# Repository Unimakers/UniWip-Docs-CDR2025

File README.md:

---
title: "README & MICRODOC"
layout: default
---
# Documentation de l'équipe UniWIP

Table de contenu:
- [Documentation de l'équipe UniWIP](#documentation-de-léquipe-uniwip)
  - [Comment créer une page ?](#comment-créer-une-page-)
  - [Comment afficher un modèle 3D](#comment-afficher-un-modèle-3d)

## Comment créer une page ?

Allez dans le dossier correspondant au thème de la page, 

exemple pour l'élec du robot principal: Robot/Elec/

Créez un nouveau fichier pour votre nouvelle page.

Rajoutez en haut du fichier:

```yaml
---
title: "Titre de votre page"
layout: technical
---
```

Utilisez `layout: technical` si vous souhaitez utiliser les modèles 3D ou le visualiseur kicad dans votre page, sinon utilisez `layout: default` pour réduire le temps de chargement de la page en supprimant les imports inutiles.

Les clés de définition doivent se trouver entre les deux `---`.
Après le deuxième `---` vous pouvez écrire le contenu de la page **en markdown**.

Vous pouvez rajouter un 
```yaml
has_children: true
```
si vous souhaitez faire de cette page une page de catégorie qui aura donc des sous-pages.

Pour mettre cette page en tant que sous-page dans une catégorie (et non à la racine) vous devez rajouter une clé `parent` et eventuellement une clé `grand_parent`:

La clé `parent` permettra de définir le parent direct de la page, la valeur doit etre le titre de la page parent.

Exemple, si vous créez une page dans la catégorie `Electronique` du `Robot` vous devrez définir la clé `parent` avec la valeur `Electronique`.

La clé `grand_parent` permettra de définir le grand parent de la page, c'est à dire la catégorie racine, la valeur doit etre le titre du grand parent.

Exemple, si vous créez une page dans la catégorie `Electronique` du `Robot` vous devrez définir la clé `grand_parent` avec la valeur `Robot`

Actuellement l'arbre des titres et catégories est:
```
Racine:
|-Présentation
|-Robot:
| |-Mécanique
| |-Stratégie
|-Pami:
| |-Mécanique
| |-Stratégie
|-Electronique
|-Programmation
| |-Déplacement
| |-Détection
```

Exemple pour créer une catégorie `Actionneurs` dans `Mécanique` sous `Robot` et ensuite créer une page `Pince`:

On crée le dossier `Robot/Meca/Actionneurs` (c'est mieux pour la lisibilité de trier les pages dans des dossiers, techniquement on pourrait tout laisser à la racine).

On crée le fichier `Robot/Meca/Actionneurs/Actionneurs.md`:
```md
---
title: Actionneurs
parent: Mécanique
grand_parent: Robot
has_children: true
layout: default
---
# Les actionneurs de notre robot
Le robot a besoin d'actionneurs pour fonctionner
```

On crée le fichier `Robot/Meca/Actionneurs/Pince.md`:
```md
---
title: Pince
parent: Actionneurs
grand_parent: Mécanique
has_children: true
layout: default
---
# La pince du robot
La pince du robot, nécessaire pour attraper.....
```

## Comment afficher un modèle 3D

Dans votre code markdown rajoutez:
```md
<model-viewer alt="Texte de déscription du modèle 3D" src="url / chemin du modèle 3D" ar shadow-intensity="1" camera-controls touch-action="pan-y"></model-viewer>

Ou

{%raw%}{{%include model3D.html alt="Texte de description du modèle 3D" model="url / chemin du modèle 3D"%}}{%endraw%}
``` 
Le modèle 3D **doit** être en format GLTF / GLB.

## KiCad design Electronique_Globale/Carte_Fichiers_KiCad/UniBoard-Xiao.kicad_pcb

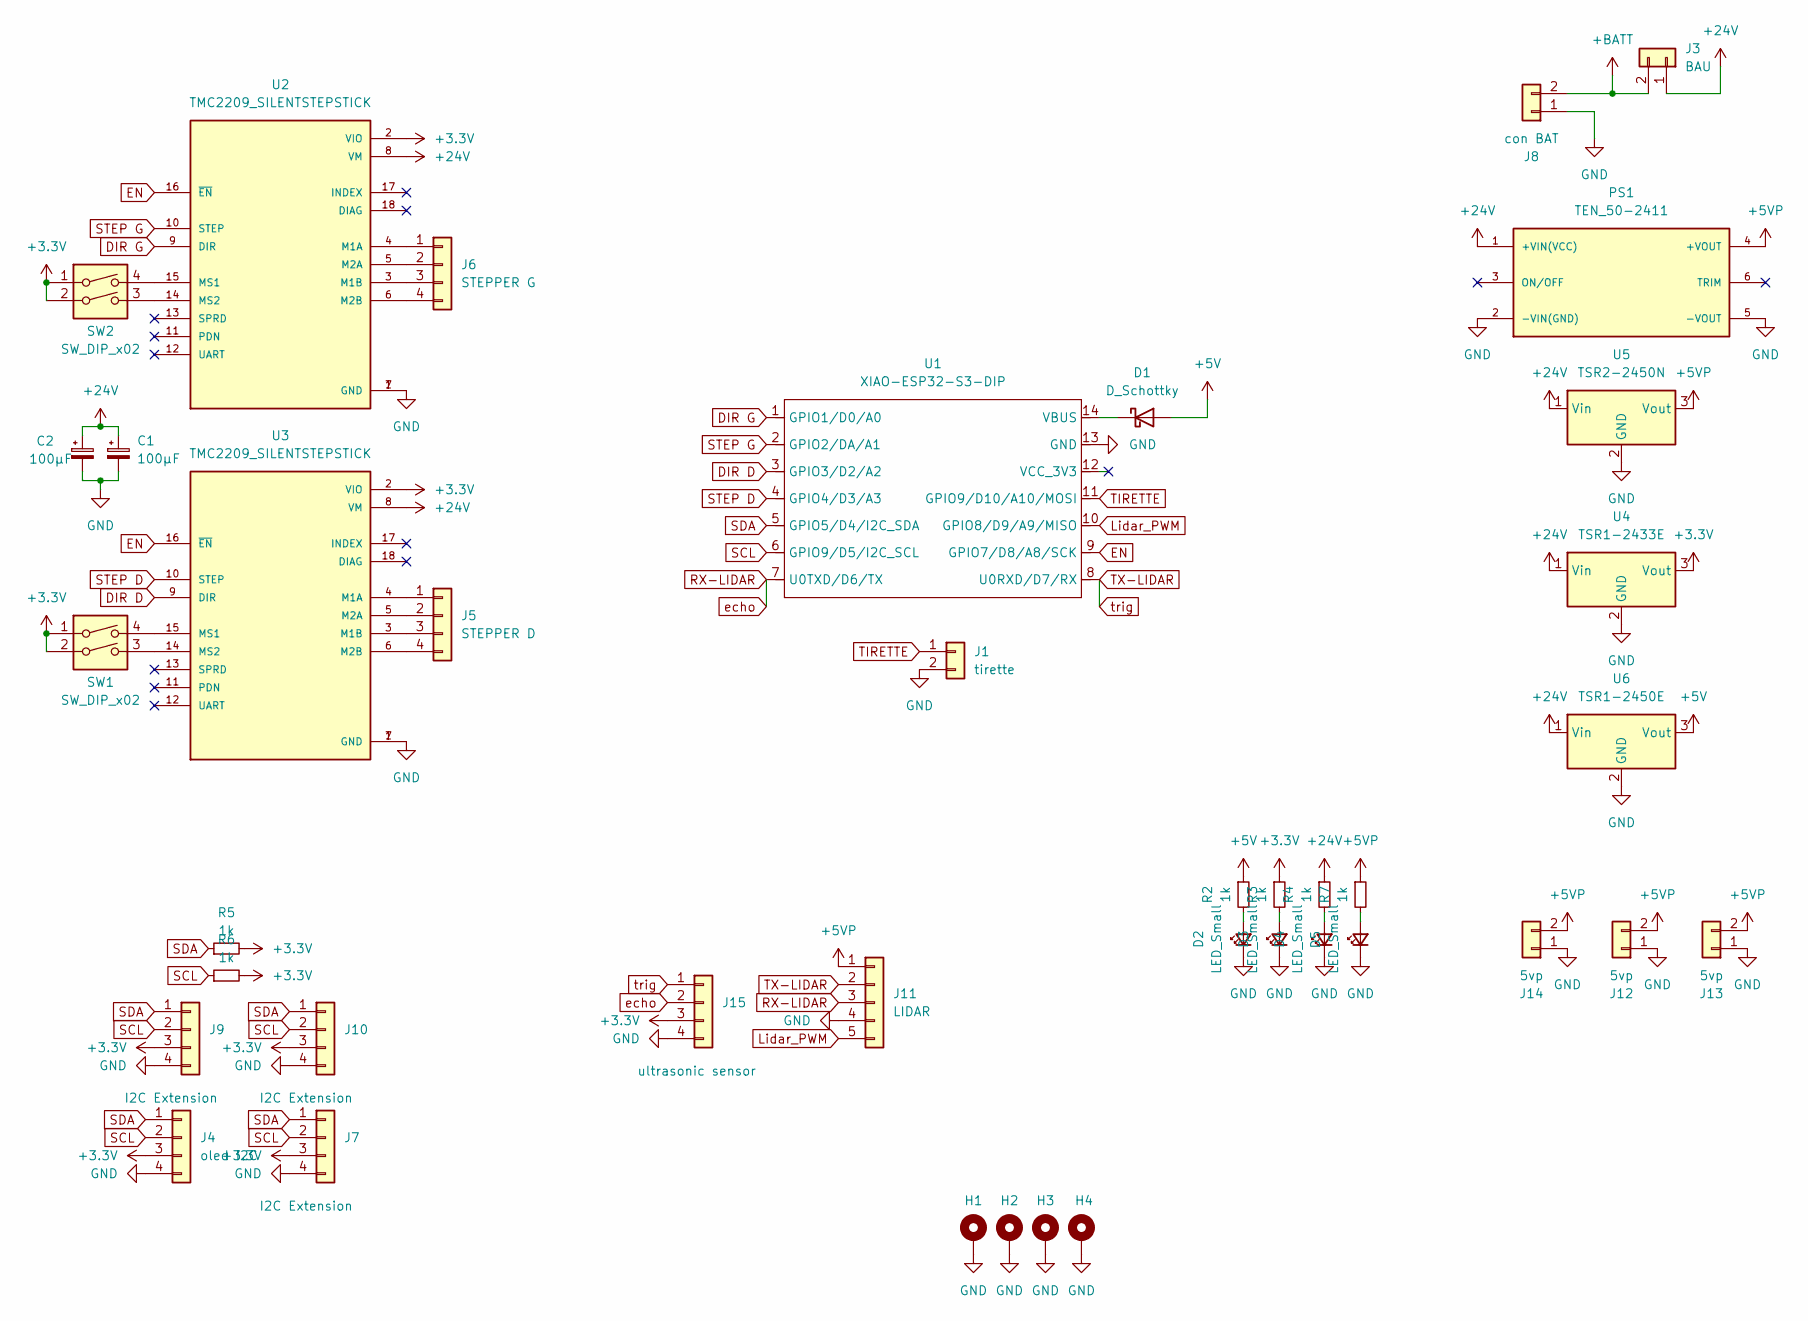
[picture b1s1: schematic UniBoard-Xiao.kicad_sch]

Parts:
C1, C2: 100µF; CP_Radial_D10.0mm_P5.00mm
D1: D_Schottky; D_A-405_P10.16mm_Horizontal
D2, D3, D4, D5: LED_Small; LED_1206_3216Metric
H1, H2, H3, H4: MountingHole_Pad; MountingHole_3.2mm_M3_Pad_Via
J1: tirette; Molex_KK-254_AE-6410-02A_1x02_P2.54mm_Vertical
J3: BAU; Molex_KK-396_A-41791-0002_1x02_P3.96mm_Vertical
J4: oled I2C; Molex_KK-254_AE-6410-04A_1x04_P2.54mm_Vertical
J5: STEPPER D; Molex_KK-254_AE-6410-04A_1x04_P2.54mm_Vertical
J6: STEPPER G; Molex_KK-254_AE-6410-04A_1x04_P2.54mm_Vertical
J7, J9, J10: I2C Extension; Molex_KK-254_AE-6410-04A_1x04_P2.54mm_Vertical
J8: con BAT; AMASS_XT60-M_1x02_P7.20mm_Vertical
J11: LIDAR; JST_XH_B5B-XH-A_1x05_P2.50mm_Vertical
J12, J13, J14: 5vp; AMASS_XT30U-F_1x02_P5.0mm_Vertical
J15: ultrasonic sensor; Molex_KK-254_AE-6410-04A_1x04_P2.54mm_Vertical
PS1: TEN_50-2411; TEN50_TRP; PARTREV February 3, 2021
R2, R3, R4, R5, R6, R7: 1k; R_1206_3216Metric_Pad1.30x1.75mm_HandSolder
SW1, SW2: SW_DIP_x02; SW_DIP_SPSTx02_Slide_9.78x7.26mm_W7.62mm_P2.54mm
U1: XIAO-ESP32-S3-DIP; XIAO-ESP32S3-DIP
U2, U3: TMC2209_SILENTSTEPSTICK; MODULE_TMC2209_SILENTSTEPSTICK; PARTREV 1.20
U4: TSR1-2433E; Converter_DCDC_TRACO_TSR1-xxxxE_THT
U5: TSR2-2450N; Converter_DCDC_TRACO_TSR2-24xxN_TSR2-24xxxN_THT
U6: TSR1-2450E; Converter_DCDC_TRACO_TSR1-xxxxE_THT

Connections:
+3.3V: J4.3, J7.3, J9.3, J10.3, J15.3, R3.1, R5.2, R6.2, SW1.1, SW1.2, SW2.1, SW2.2, U2.2 (VIO), U3.2 (VIO), U4.3 (Vout)
+5V: D1.2 (A), R2.1, U6.3 (Vout)
+5VP: J11.1, J12.2, J13.2, J14.2, PS1.4 (+VOUT), R7.1, U5.3 (Vout)
+24V: C1.1, C2.1, J3.1, PS1.1 (+VIN(VCC)), R4.1, U2.8 (VM), U3.8 (VM), U4.1 (Vin), U5.1 (Vin), U6.1 (Vin)
+BATT: J3.2, J8.2
DIR D: U1.3 (GPIO3/D2/A2), U3.9 (DIR)
DIR G: U1.1 (GPIO1/D0/A0), U2.9 (DIR)
EN: U1.9 (GPIO7/D8/A8/SCK), U2.16 (~EN), U3.16 (~EN)
GND: C1.2, C2.2, D2.1 (K), D3.1 (K), D4.1 (K), D5.1 (K), H1.1, H2.1, H3.1, H4.1, J1.2, J4.4, J7.4, J8.1, J9.4, J10.4, J11.4, J12.1, J13.1, J14.1, J15.4, PS1.2 (-VIN(GND)), PS1.5 (-VOUT), U1.13 (GND), U2.1 (GND), U2.7 (GND), U3.1 (GND), U3.7 (GND), U4.2 (GND), U5.2 (GND), U6.2 (GND)
Lidar_PWM: J11.5, U1.10 (GPIO8/D9/A9/MISO)
unnamed: D1.1 (K), U1.14 (VBUS)
unnamed: D2.2 (A), R2.2
unnamed: D3.2 (A), R3.2
unnamed: D4.2 (A), R4.2
unnamed: D5.2 (A), R7.2
unnamed: J5.1, U3.4 (M1A)
unnamed: J5.2, U3.5 (M2A)
unnamed: J5.3, U3.3 (M1B)
unnamed: J5.4, U3.6 (M2B)
unnamed: J6.1, U2.4 (M1A)
unnamed: J6.2, U2.5 (M2A)
unnamed: J6.3, U2.3 (M1B)
unnamed: J6.4, U2.6 (M2B)
unnamed: SW2.4, U2.15 (MS1)
unnamed: SW2.3, U2.14 (MS2)
unnamed: SW1.4, U3.15 (MS1)
unnamed: SW1.3, U3.14 (MS2)
RX-LIDAR: J11.3, J15.2, U1.7 (U0TXD/D6/TX)
SCL: J4.2, J7.2, J9.2, J10.2, R6.1, U1.6 (GPIO9/D5/I2C_SCL)
SDA: J4.1, J7.1, J9.1, J10.1, R5.1, U1.5 (GPIO5/D4/I2C_SDA)
STEP D: U1.4 (GPIO4/D3/A3), U3.10 (STEP)
STEP G: U1.2 (GPIO2/DA/A1), U2.10 (STEP)
TIRETTE: J1.1, U1.11 (GPIO9/D10/A10/MOSI)
TX-LIDAR: J11.2, J15.1, U1.8 (U0RXD/D7/RX)

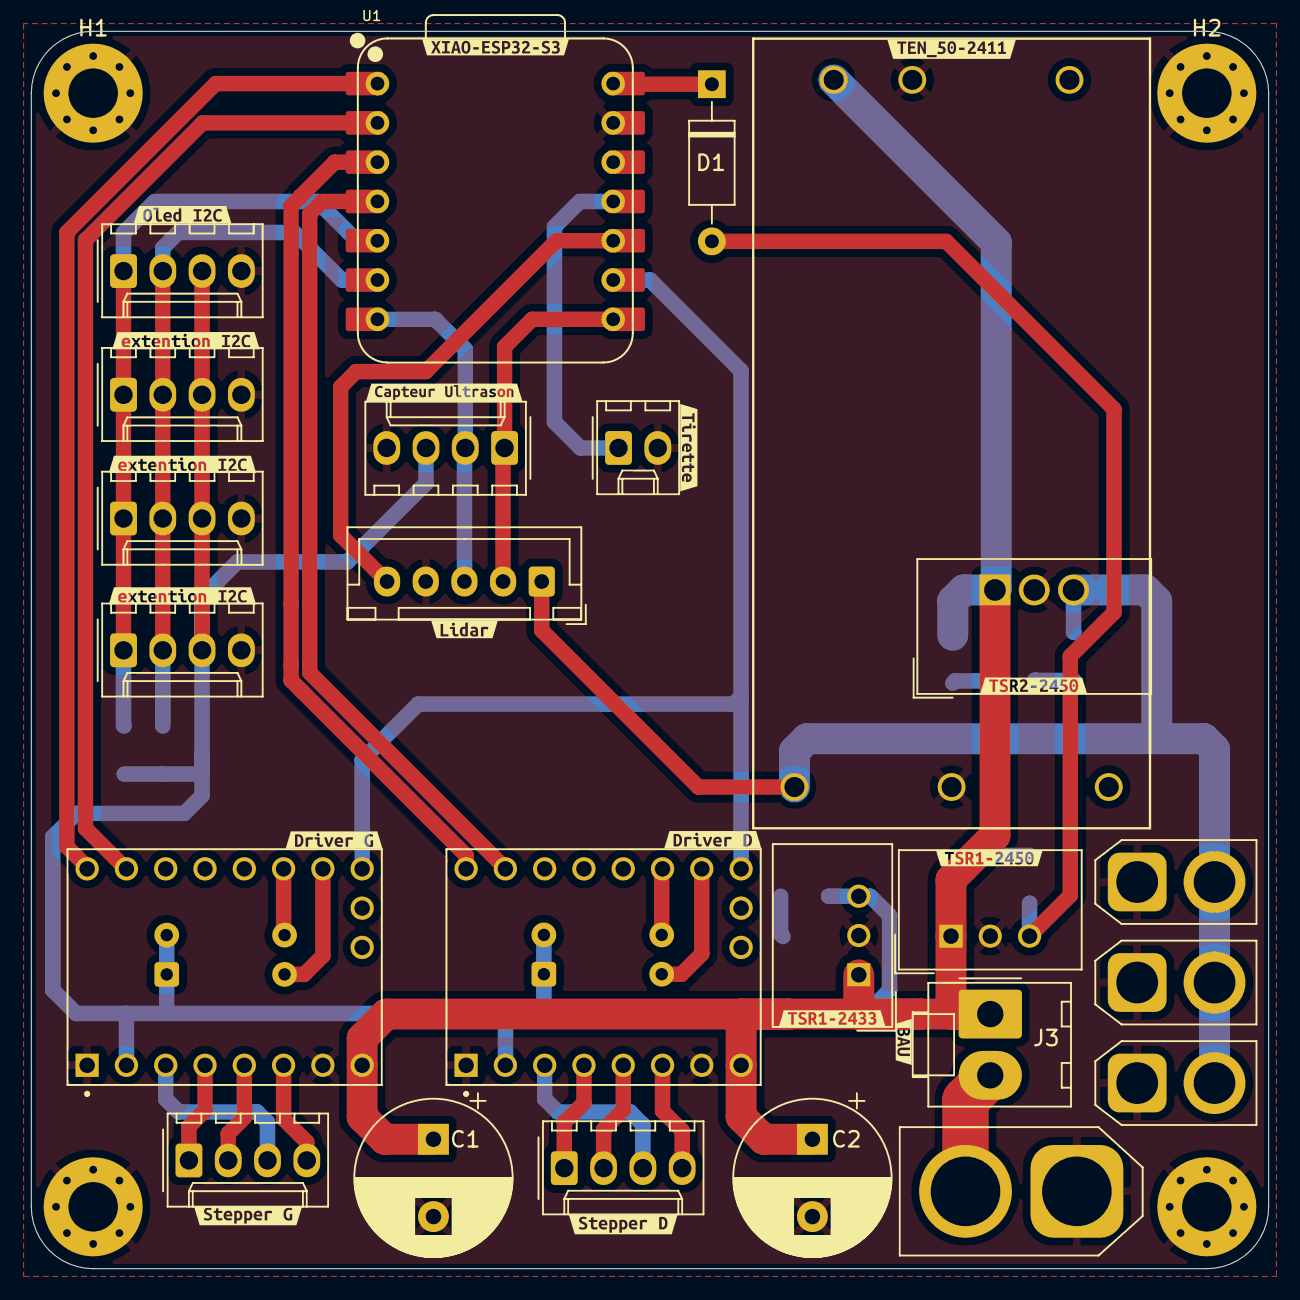
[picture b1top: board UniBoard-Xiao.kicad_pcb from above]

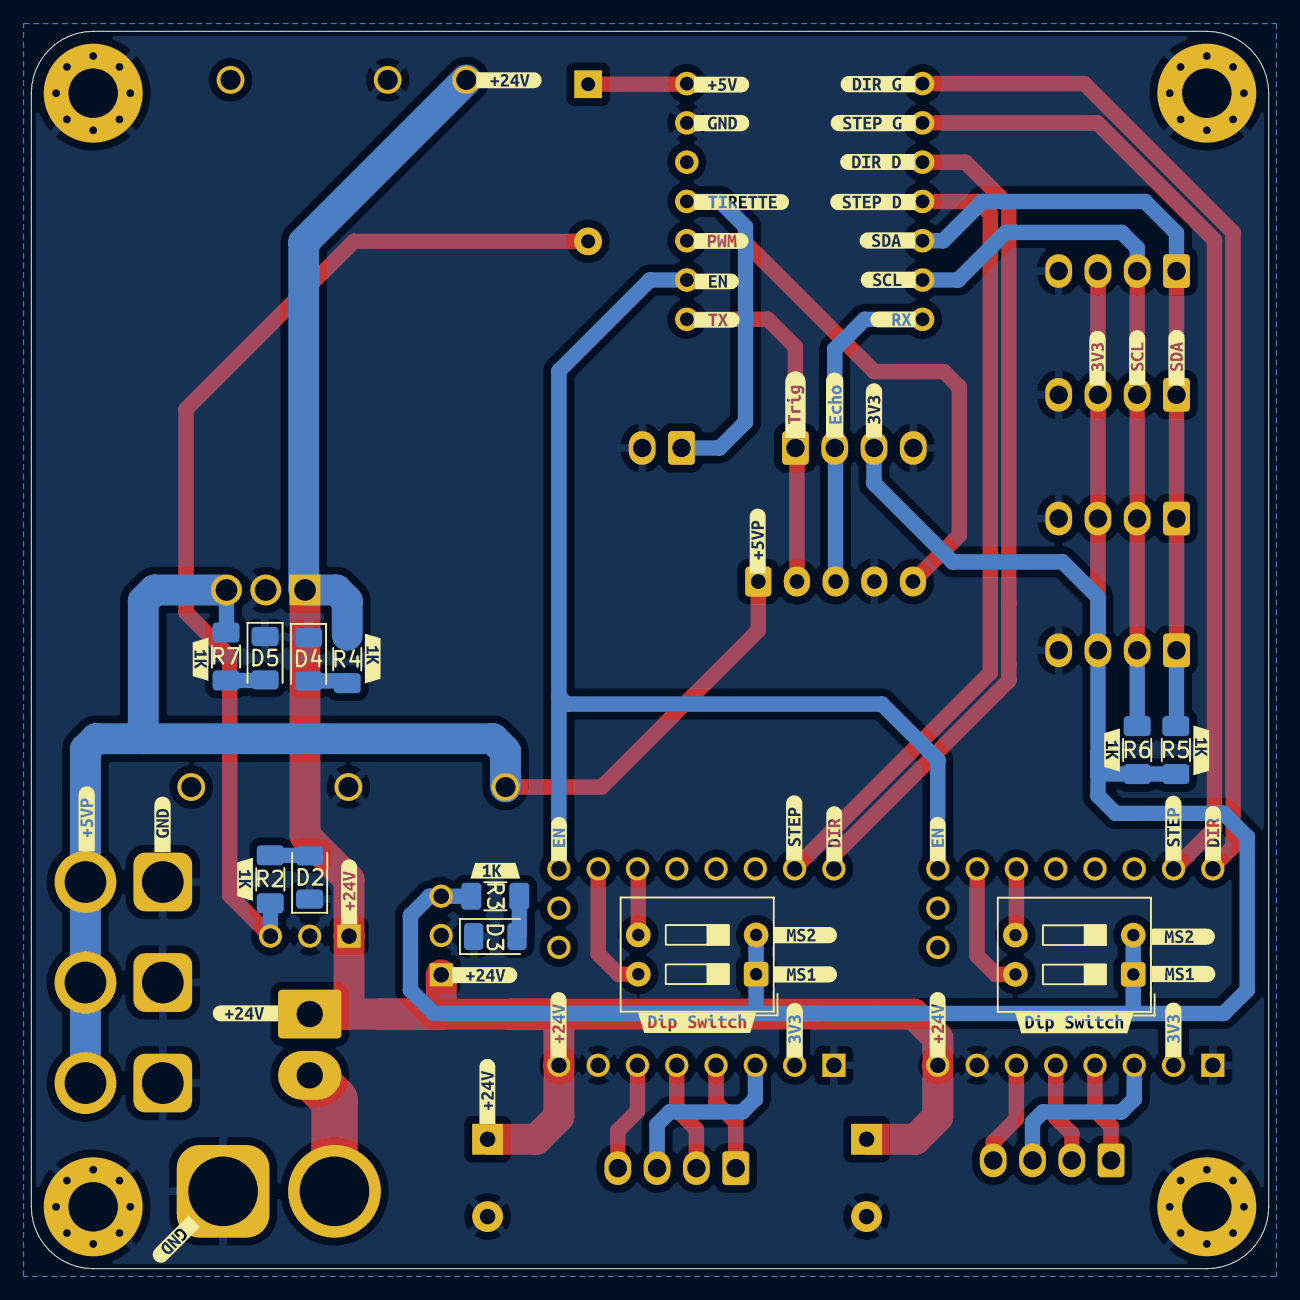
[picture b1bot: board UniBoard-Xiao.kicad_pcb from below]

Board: 2 copper layers, 80.0 x 80.0 mm, 107 parts (62 on the bottom side), 34 nets.

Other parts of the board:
kibuzzard-67ED5DC2: G***; kibuzzard-67ED5DC2
kibuzzard-67ED5E7B, kibuzzard-67ED5E7B#2, kibuzzard-67ED5E7B#3, kibuzzard-67ED5E7B#4: G***; kibuzzard-67ED5E7B
kibuzzard-67ED5E8C: G***; kibuzzard-67ED5E8C
kibuzzard-67ED5E55, kibuzzard-67ED5E55#2, kibuzzard-67ED5E55#3: G***; kibuzzard-67ED5E55
kibuzzard-67ED5EA2: G***; kibuzzard-67ED5EA2
kibuzzard-67ED5FB9: G***; kibuzzard-67ED5FB9
kibuzzard-67ED5FC6, kibuzzard-67ED5FC6#2: G***; kibuzzard-67ED5FC6
kibuzzard-67ED7EA6: G***; kibuzzard-67ED7EA6
kibuzzard-67ED7EC9: G***; kibuzzard-67ED7EC9
kibuzzard-67ED8D8D, kibuzzard-67ED8D8D#2: G***; kibuzzard-67ED8D8D
kibuzzard-67ED8D70: G***; kibuzzard-67ED8D70
kibuzzard-67ED8DB2, kibuzzard-67ED8DB2#2: G***; kibuzzard-67ED8DB2
kibuzzard-67ED8DD6, kibuzzard-67ED8DD6#2: G***; kibuzzard-67ED8DD6
kibuzzard-67ED60FC: G***; kibuzzard-67ED60FC
kibuzzard-67ED61B4: G***; kibuzzard-67ED61B4
kibuzzard-67ED70B6: G***; kibuzzard-67ED70B6
kibuzzard-67ED71A8: G***; kibuzzard-67ED71A8
kibuzzard-67ED71B1: G***; kibuzzard-67ED71B1
kibuzzard-67ED71DE: G***; kibuzzard-67ED71DE
kibuzzard-67ED72B0: G***; kibuzzard-67ED72B0
kibuzzard-67ED72B6: G***; kibuzzard-67ED72B6
kibuzzard-67ED72F3: G***; kibuzzard-67ED72F3
kibuzzard-67ED72FD: G***; kibuzzard-67ED72FD
kibuzzard-67ED80BA, kibuzzard-67ED80BA#2: G***; kibuzzard-67ED80BA
kibuzzard-67ED86A2: G***; kibuzzard-67ED86A2
kibuzzard-67ED86A7: G***; kibuzzard-67ED86A7
kibuzzard-67ED86B0: G***; kibuzzard-67ED86B0
kibuzzard-67ED86BE: G***; kibuzzard-67ED86BE
kibuzzard-67ED86D2: G***; kibuzzard-67ED86D2
kibuzzard-67ED86DD: G***; kibuzzard-67ED86DD
kibuzzard-67ED90FC, kibuzzard-67ED90FC#2, kibuzzard-67ED90FC#3: G***; kibuzzard-67ED90FC
kibuzzard-67ED725F: G***; kibuzzard-67ED725F
kibuzzard-67ED911B, kibuzzard-67ED911B#2, kibuzzard-67ED911B#3: G***; kibuzzard-67ED911B
kibuzzard-67ED922B: G***; kibuzzard-67ED922B
kibuzzard-67ED6169, kibuzzard-67ED6169#2, kibuzzard-67ED6169#3: G***; kibuzzard-67ED6169
kibuzzard-67ED6224: G***; kibuzzard-67ED6224
kibuzzard-67ED7493: G***; kibuzzard-67ED7493
kibuzzard-67ED8061, kibuzzard-67ED8061#2, kibuzzard-67ED8061#3, kibuzzard-67ED8061#4, kibuzzard-67ED8061#5, kibuzzard-67ED8061#6: G***; kibuzzard-67ED8061
kibuzzard-67ED8412: G***; kibuzzard-67ED8412
kibuzzard-67ED8447: G***; kibuzzard-67ED8447
kibuzzard-67ED8456: G***; kibuzzard-67ED8456
kibuzzard-67ED8466: G***; kibuzzard-67ED8466
kibuzzard-67ED8504: G***; kibuzzard-67ED8504
kibuzzard-67ED8648: G***; kibuzzard-67ED8648
kibuzzard-67EE6BB1: G***; kibuzzard-67EE6BB1
kibuzzard-67EE6BB9: G***; kibuzzard-67EE6BB9

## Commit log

2025-06-03 init (copy from another cdr team docs site I made)
2025-06-03 I don't know
2025-06-05 edit config
2025-06-05 feat: unimakers theme and elec kicanvas
2025-06-05 fix: change layout to technical
2025-06-05 fix:nav_order feat:add stratégie instead of prog and put prog at root
2025-06-05 feat:add meca and model-viewer and fichiersgltf folders
2025-06-05 adsds
2025-06-05 test
2025-06-05 robotupdate
2025-06-05 mdfix
2025-06-05 feat: add docs of programation
2025-06-11 feat: add robot 3D model & fix:a lot of things
2025-06-11 fix: some fixes
2025-06-11 fix: zoom max on robot
2025-06-12 move
2025-06-12 add link to unimakers website
2025-06-12 update elec
2025-06-12 welcome back Robot
2025-06-12 update robot règlement et actionneurs
2025-06-12 elec update
2025-06-12 Update Robot images
2025-06-12 LES S BORDELS
2025-06-12 fix: pami wasn't technical layout
2025-06-12 fix: bad file name in pami for 3D model
2025-06-12 maj pami
2025-06-12 encore du texte
2025-06-12 du texte encore
2025-06-12 fin pamis md
2025-06-12 pamis
2025-06-12 pami
2025-06-13 update homologation
2025-06-13 Update actionneur suppr
2025-06-13 Update actionneur
2025-06-13 Update images
2025-06-13 Update mise en page
2025-06-13 Update mise en page regles
2025-06-13 Update titre image
2025-06-13 index init
2025-06-13 Update suppr regles
2025-06-13 Update suppr homologation
2025-06-13 Update ajout homologation et regles
2025-06-13 ça fait beaucoup de photos quand meme
2025-06-13 Update presentation.md
    (text written by jade)
2025-06-14 photo actionneur
2025-06-14 fixes
2025-06-15 meca
2025-06-15 Update glb robot file
2025-06-15 meca pam
2025-06-15 il est pas si tard
2025-06-15 test 3
2025-06-15 il est encore tôt
2025-06-16 In the jungle, rilès
2025-06-16 tiekar,bekar
2025-06-16 sfxj
